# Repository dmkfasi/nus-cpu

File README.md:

# nus-cpu

This is my own yet another attempt to re-create Nintendo 64 motherboard for a portable, tablet or bartop mod.

I am going after for as much as possible: modular design, reuse of original components, cheapest production costs and the best visual display picture.

There are many bright minds out there whose ideas I try to adopt and develop further. But since I lack of expertise on several electronics topics, this whole thing definately will need some tune up.

Feel free to use, share and modify!

# Work in progress
Schematics is not verified so far, but it looks complete and legit and came from a more or less reliable source off a retrogaming community board. Everything has been broken down into following components:
* CPU-RCP defines core:
    * CPU to RCP connections;
    * RCP to PIF (Nintendo peripherials controller);
    * PIF to Controller Pak;
    * Power rails, ENABLE delay and /COLDRESET circuit, decoupling capacitors;
    * and breakout connections to external peripherial devices:
        * Gamepak port, 50pin;
        * RDRAM interface, 30pin;
        * Audio DAC, 4pin;
        * Video DAC, 10pin;
        * and Controller pak (two players), 4pin.
* RCP-RDRAM defines RAM interface:
    * Uses of two or four chips:
        * 2 of RDRAM18;
        * 4 of RDRAM18;
        * 2 of RDRAM36.
    * and onboard MX8330 clock generator;
* RCP-CART defines Gamepak interface, simple board with flat cable connector;
* RCP-SND defines audio output interface, either usage of B9480F or any other DAC and amplifier;
* RCP-VDC will define video interface.

# PCB design and production files
* CPU-RCP is 4 layer board, finished, Gerber files are included;

* RCP-RDRAM is 4 layer board, finished, Gerber files are included;

* RCP-CART is 2 layer board, finished, Gerber files are included;

* RCP-SND is not started yet;
* RCP-VDC is not started yet;

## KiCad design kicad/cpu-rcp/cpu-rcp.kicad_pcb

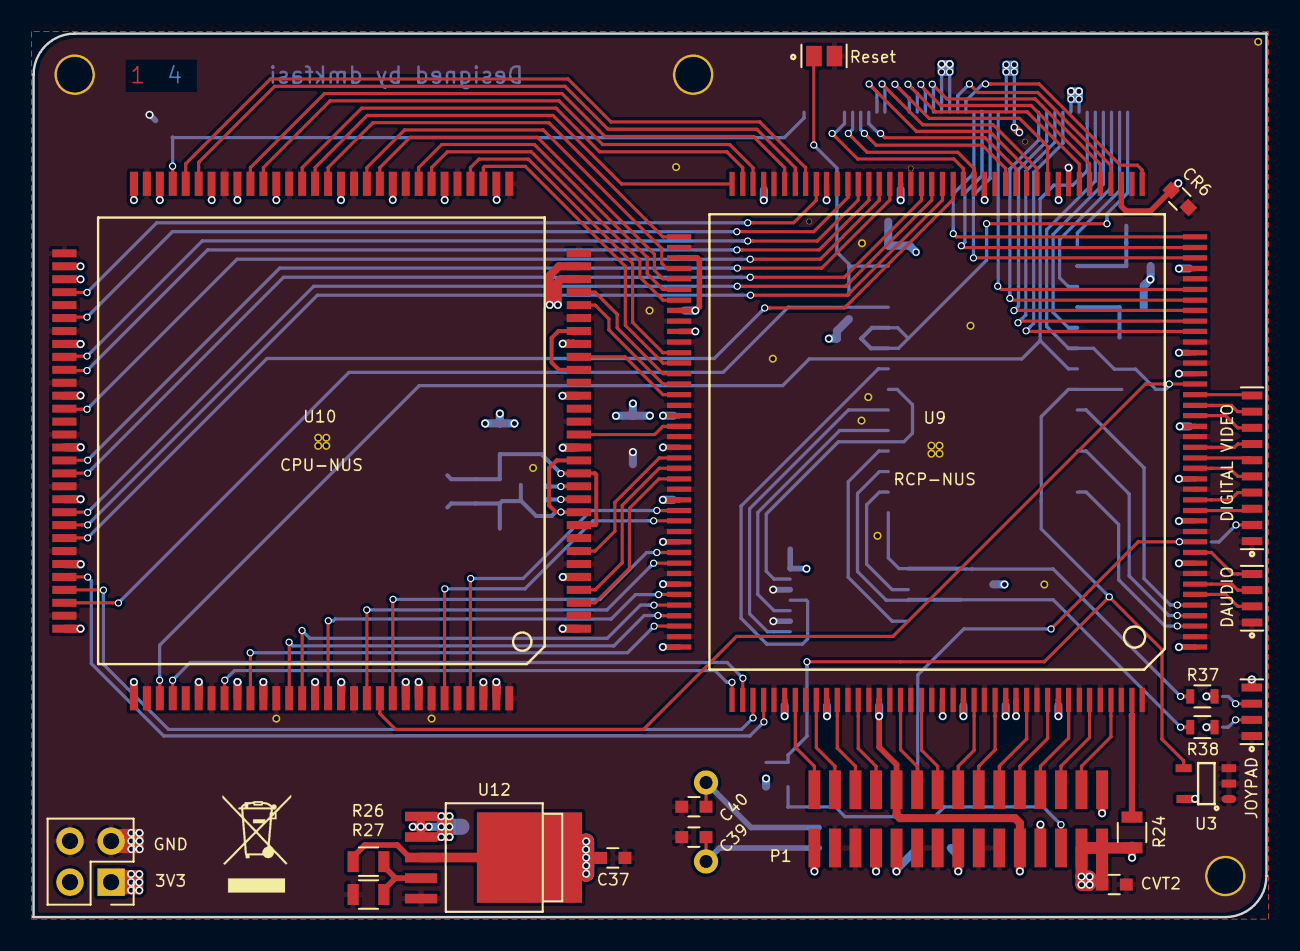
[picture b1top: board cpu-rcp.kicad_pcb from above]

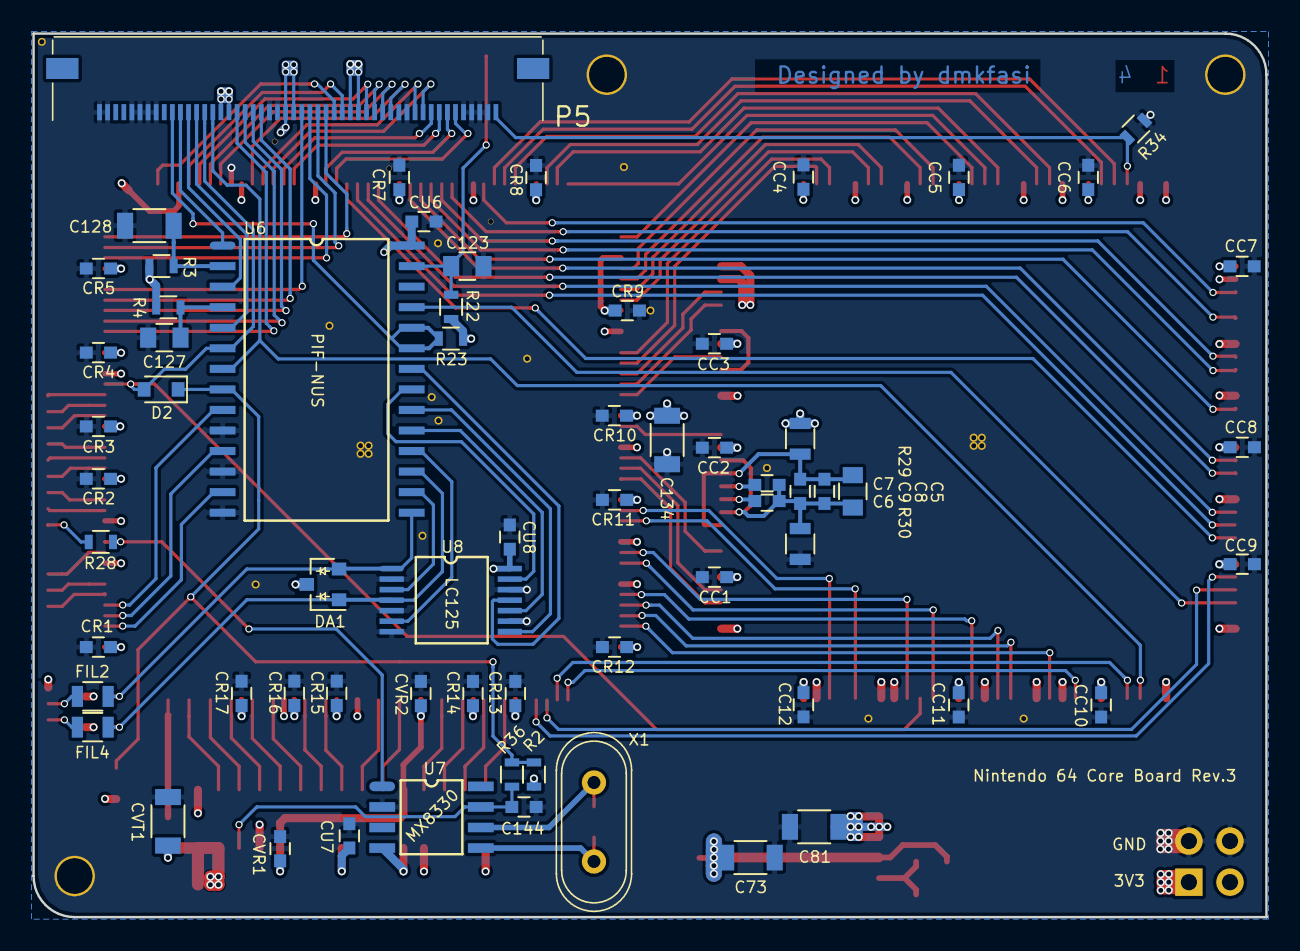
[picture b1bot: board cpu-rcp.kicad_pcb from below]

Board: 4 copper layers, 76.2 x 54.6 mm, 85 parts (65 on the bottom side), 127 nets.

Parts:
C5: C_0805
C6, C7: 220pF; C_0603
C8, C9, C144: C_0603
C37: .1uF; C_0603
C39, C40: 40pF; C_0603
C73, C81, C134: 68uF; C_1206
C123, C127: ±; C_0805
C128: 10uF; C_1206
CC1, CC2, CC3, CC4, CC5, CC6, CC7, CC8, CC9, CC10, CC11, CC12: .1uF; C_0603
CR1, CR2, CR3, CR4, CR5, CR6, CR7, CR8, CR9, CR10, CR11, CR12, CR13, CR14, CR15, CR16, CR17: .1uF; C_0603
CU6, CU7, CU8: .1uF; C_0603
CVR1, CVR2: .1uF; C_0603
CVT1: 10uF; C_1206
CVT2: .1uF; C_0603
D2: ±; D_0805
DA1: BAC54; D_SOT-23_AAK
DAUD1: DAUDIO; Connectors_GS4
DCIN1: Power Input; Pin_Header_Straight_2x02_Pitch2.54mm
DVO1: DIGITAL VIDEO; Connectors_GS10
FIL2, FIL4: 3.3uH; L_0805
JOY1: JOYPAD; Connectors_GS4
P1: RDRAM-EDGE; rdram-edge-smt
P5: 502790-5091; connector-molex-502790-5091
R2: 2K; R_0603
R3: 30K; R_0603
R4: 68K; R_0603
R22, R34: 47K; R_0603
R23: 1K; R_0603
R24: 24R; R_0805
R26: 316; R_0805
R27: 301; R_0805
R28: 0R; R_0603
R29, R30: 4R7; R_0805
R36: 51K; R_0603
R37, R38: 750R; R_0603
SW1: Reset; Connectors_GS2
U3: U3; u3-sot-23-5
U6: PIF-NUS; pif-nus-so-28w
U7: MX8330; mx8330-sop-8
U8: LC125; u8-ssop-14
U9: RCP-NUS; rcp-nus-qfp-160
U10: CPU-NUS; cpu-nus-qfp-120
U12: PQ7VZ5; d-pak-5
X1: 14.318MHz; Crystal_HC-49V

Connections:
+3V3: C81.1, C134.1, CC1.1, CC2.1, CC3.1, CC4.1, CC5.1, CC6.1, CC7.1, CC8.1, CC9.1, CC10.1, CC11.1, CC12.1, CR1.1, CR2.1, CR3.1, CR4.1, CR5.1, CR6.1, CR7.1, CR8.1, CR9.1, CR10.1, CR11.1, CR12.1, CR13.1, CR14.1, CR15.1, CR16.1, CR17.1, CU6.1, CU7.1, CU8.1, DA1.3, DCIN1.1, DCIN1.2, JOY1.4, P1.15, P1.19, P1.23, P1.26, P1.27, P1.30, P5.18, P5.19, P5.26, P5.27, P5.34, P5.35, R2.1, R3.2, R4.2, R22.1, R23.1, R29.2, R37.1, R38.1, U3.5, U6.28, U7.4, U8.14, U9.1, U9.9, U9.13, U9.17, U9.22, U9.27, U9.29, U9.37, U9.43, U9.49, U9.56, U9.64, U9.71, U9.77, U9.83, U9.88, U9.90, U9.98, U9.101, U9.106, U9.110, U9.114, U9.120, U9.126, U9.130, U9.141, U9.143, U9.147, U9.148, U9.152, U10.1, U10.5, U10.15, U10.19, U10.23, U10.28, U10.29, U10.32, U10.36, U10.40, U10.44, U10.49, U10.52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
//EOK: U9.60, U10.82
//PVALID: U9.62, U10.78
/CART_READ: P5.20, U9.44
/CART_WRITE: P5.16, U9.46
/COLDRESET: D2.2, P5.37, U6.6, U9.26, U10.110
/DSYNC: DVO1.3, U9.14
/INT0: U9.80, U10.46
/INT2: U6.25, U10.88
/MasterClock: U9.99, U10.16
/NMI: P5.36, U6.7, U10.93
/SYSAD0: U9.66, U10.73
/SYSAD1: U9.67, U10.70
/SYSAD2: U9.68, U10.69
/SYSAD3: U9.69, U10.66
/SYSAD4: U9.72, U10.64
/SYSAD5: U9.73, U10.56
/SYSAD6: U9.74, U10.55
/SYSAD7: U9.75, U10.51
/SYSAD8: U9.78, U10.50
/SYSAD9: U9.79, U10.47
/SYSAD10: U9.81, U10.45
/SYSAD11: U9.84, U10.42
/SYSAD12: U9.85, U10.41
/SYSAD13: U9.86, U10.38
/SYSAD14: U9.87, U10.37
/SYSAD15: U9.92, U10.34
/SYSAD16: U9.93, U10.33
/SYSAD17: U9.94, U10.27
/SYSAD18: U9.95, U10.26
/SYSAD19: U9.96, U10.22
/SYSAD20: U9.102, U10.7
/SYSAD21: U9.103, U10.4
/SYSAD22: U9.104, U10.3
/SYSAD23: U9.107, U10.117
/SYSAD24: U9.108, U10.115
/SYSAD25: U9.121, U10.98
/SYSAD26: U9.122, U10.94
/SYSAD27: U9.123, U10.87
/SYSAD28: U9.124, U10.86
/SYSAD29: U9.59, U10.83
/SYSAD30: U9.61, U10.81
/SYSAD31: U9.65, U10.77
/SYSCMD0: U9.118, U10.100
/SYSCMD1: U9.117, U10.103
/SYSCMD2: U9.115, U10.106
/SYSCMD3: U9.112, U10.109
/SYSCMD4: U9.111, U10.111
ADDR: P1.12, U9.153
BCLK: DAUD1.2, U9.6
CART_ADDR00: P5.7, U9.57
CART_ADDR01: P5.9, U9.53
CART_ADDR02: P5.11, U9.51
CART_ADDR03: P5.15, U9.47
CART_ADDR04: P5.23, U9.39
CART_ADDR05: P5.25, U9.35
CART_ADDR06: P5.31, U9.33
CART_ADDR07: P5.33, U9.31
CART_ADDR08: P5.32, U9.32
CART_ADDR09: P5.30, U9.34
CART_ADDR10: P5.24, U9.38
CART_ADDR11: P5.22, U9.40
CART_ADDR12: P5.14, U9.50
CART_ADDR13: P5.10, U9.52
CART_ADDR14: P5.8, U9.54
CART_ADDR15: P5.6, U9.58
CART_ALE_H: P5.21, U9.41
CART_ALE_L: P5.17, U9.45
CIC_CLK: P5.40, U6.1
CIC_IN: P5.38, U6.5
CIC_OUT: P5.39, U6.3
CMD: P1.6, U9.137
DQ0: P1.1, U9.127
DQ1: P1.2, U9.129
DQ2: P1.3, U9.131
DQ3: P1.4, U9.133
DQ4: P1.7, U9.139
DQ5: P1.10, U9.149
DQ6: P1.11, U9.151
DQ7: P1.13, U9.155
DQ8: P1.14, U9.157
EEPROM_DAT: P5.41, R23.2, U6.23, U6.24
ENABLE: D2.1, R2.2, R36.2, U3.4, U6.8
ENABLE_CLK: C144.1, P1.18, R36.1, U7.7
GND: C37.2, C39.2, C40.2, C73.2, C81.2, C123.2, C127.2, C128.2, C134.2, C144.2, CC1.2, CC2.2, CC3.2, CC4.2, CC5.2, CC6.2, CC7.2, CC8.2, CC9.2, CC10.2, CC11.2, CC12.2, CR1.2, CR2.2, CR3.2, CR4.2, CR5.2, CR6.2, CR7.2, CR8.2, CR9.2, CR10.2, CR11.2, CR12.2, CR13.2, CR14.2, CR15.2, CR16.2, CR17.2, CU6.2, CU7.2, CU8.2, CVR1.2, CVR2.2, CVT1.2, CVT2.2, DAUD1.1, DCIN1.3, DCIN1.4, DVO1.1, JOY1.1, P1.21, P1.22, P1.24, P1.25, P1.28, P1.29, P5.2, P5.3, P5.4, P5.5, P5.12, P5.13, P5.28, P5.29, P5.43, P5.44, P5.45, P5.46, P5.49, P5.50, R27.2, R30.2, R34.1, SW1.2, U3.1, U3.2, U3.3, U6.10, U6.12, U6.14, U7.2, U8.2, U8.5, U8.7, U8.9, U8.12, U9.2, U9.8, U9.12, U9.16, U9.21, U9.28, U9.30, U9.36, U9.42, U9.48, U9.55, U9.63, U9.70, U9.76, U9.82, U9.89, U9.91, U9.97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
JOY1_DATA: DA1.1, FIL2.1, R37.2, U6.15, U8.1
JOY2_DATA: DA1.2, FIL4.1, R38.2, U6.17, U8.4
JTCK: P5.1, R34.2, U10.57
LRCLK: DAUD1.4, U9.10
unnamed: C5.1, C8.1, C9.1, R29.1, U10.9, U10.13
unnamed: C5.2, C6.2, C7.1, C8.2, C9.2, R30.1, U10.10, U10.14
unnamed: C6.1, U10.11
unnamed: C7.2, U10.12
unnamed: C39.1, U7.5, X1.1
unnamed: C40.1, U7.6, X1.2
unnamed: C123.1, R22.2, SW1.1, U6.27
unnamed: C127.1, R4.1, U6.4
unnamed: C128.1, R3.1, U6.2
unnamed: DVO1.2, R28.2
unnamed: FIL2.2, JOY1.3
unnamed: FIL4.2, JOY1.2
unnamed: R24.2, U9.159
unnamed: R26.2, R27.1, U12.4
unnamed: U6.16, U8.3
unnamed: U6.18, U8.6
unnamed: U6.19, U8.10
unnamed: U6.20, U8.8
unnamed: U6.21, U8.13
unnamed: U6.22, U8.11
unnamed: U10.21, U10.24
unnamed: U9.116, U10.104
PIF_ADR: U6.11, U9.4
PIF_CLK: U6.9, U9.5
PIF_DAT: U6.13, U9.3
RXCLK: P1.9, U9.146
SDAT: DAUD1.3, U9.7
SRGB0: DVO1.10, U9.25
SRGB1: DVO1.9, U9.24
SRGB2: DVO1.8, U9.23
SRGB3: DVO1.7, U9.20
SRGB4: DVO1.6, U9.19
SRGB5: DVO1.5, U9.18
SRGB6: DVO1.4, U9.15
TXCLK: P1.8, U9.144
VCLK: R28.1, U7.1, U9.11
VREF: CVR1.1, CVR2.1, P1.5, P1.20, U9.135
VTERM: C37.1, C73.1, CVT1.1, CVT2.1, P1.16, P1.17, R24.1, R26.1, U12.3

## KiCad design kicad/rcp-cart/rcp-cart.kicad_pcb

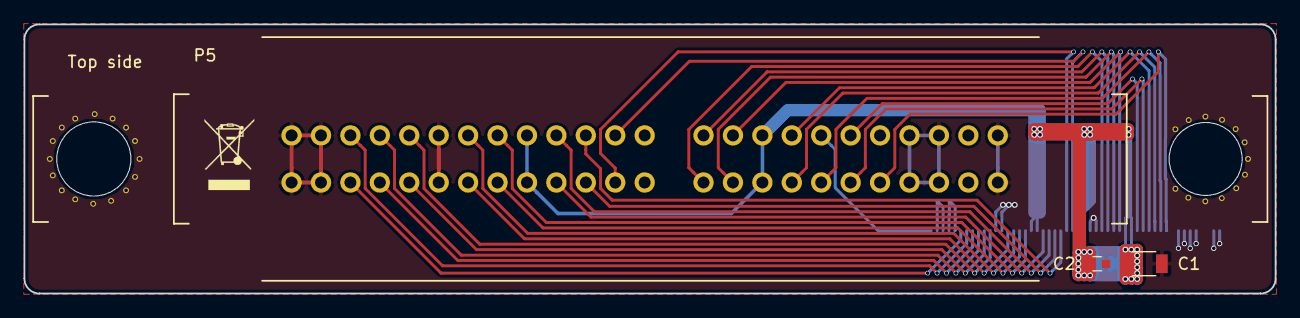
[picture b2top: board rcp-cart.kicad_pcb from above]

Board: 2 copper layers, 106.3 x 22.9 mm, 4 parts (1 on the bottom side), 29 nets.

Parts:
C1: 4.7uF; C_1206
C2: .1uF; C_0603
P5: CART-EDGE; cart-edge-2x25-2.54mm
TO MAIN BOARD: 502790-5091; connector-molex-502790-5091

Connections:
+3V3: C1.1, C2.1, P5.9, P5.17, P5.34, P5.42, TO MAIN BOARD.16, TO MAIN BOARD.17, TO MAIN BOARD.24, TO MAIN BOARD.25, TO MAIN BOARD.32, TO MAIN BOARD.33
//CART_READ: P5.10, TO MAIN BOARD.31
//CART_WRITE: P5.8, TO MAIN BOARD.35
//COLDRESET: P5.20, TO MAIN BOARD.14
//NMI: P5.45, TO MAIN BOARD.15
/CART_ADDR00: P5.28, TO MAIN BOARD.44
/CART_ADDR01: P5.29, TO MAIN BOARD.42
/CART_ADDR02: P5.30, TO MAIN BOARD.40
/CART_ADDR03: P5.32, TO MAIN BOARD.36
/CART_ADDR04: P5.36, TO MAIN BOARD.28
/CART_ADDR05: P5.37, TO MAIN BOARD.26
/CART_ADDR06: P5.40, TO MAIN BOARD.20
/CART_ADDR07: P5.41, TO MAIN BOARD.18
/CART_ADDR08: P5.16, TO MAIN BOARD.19
/CART_ADDR09: P5.15, TO MAIN BOARD.21
/CART_ADDR10: P5.12, TO MAIN BOARD.27
/CART_ADDR11: P5.11, TO MAIN BOARD.29
/CART_ADDR12: P5.7, TO MAIN BOARD.37
/CART_ADDR13: P5.5, TO MAIN BOARD.41
/CART_ADDR14: P5.4, TO MAIN BOARD.43
/CART_ADDR15: P5.3, TO MAIN BOARD.45
/CART_ALE_H: P5.35, TO MAIN BOARD.30
/CART_ALE_L: P5.33, TO MAIN BOARD.34
/CIC_CLK: P5.19, TO MAIN BOARD.11
/EEPROM_DAT: P5.21, TO MAIN BOARD.10
/JTCK: P5.44, TO MAIN BOARD.50
/PIF_CIC_DAT_IN: P5.43, TO MAIN BOARD.13
/PIF_CIC_DAT_OUT: P5.18, TO MAIN BOARD.12
GND: C1.2, C2.2, P5.1, P5.2, P5.6, P5.22, P5.23, P5.25, P5.26, P5.27, P5.31, P5.47, P5.48, P5.50, TO MAIN BOARD.1, TO MAIN BOARD.2, TO MAIN BOARD.5, TO MAIN BOARD.6, TO MAIN BOARD.7, TO MAIN BOARD.8, TO MAIN BOARD.22, TO MAIN BOARD.23, TO MAIN BOARD.38, TO MAIN BOARD.39, TO MAIN BOARD.46, TO MAIN BOARD.47, TO MAIN BOARD.48, TO MAIN BOARD.49

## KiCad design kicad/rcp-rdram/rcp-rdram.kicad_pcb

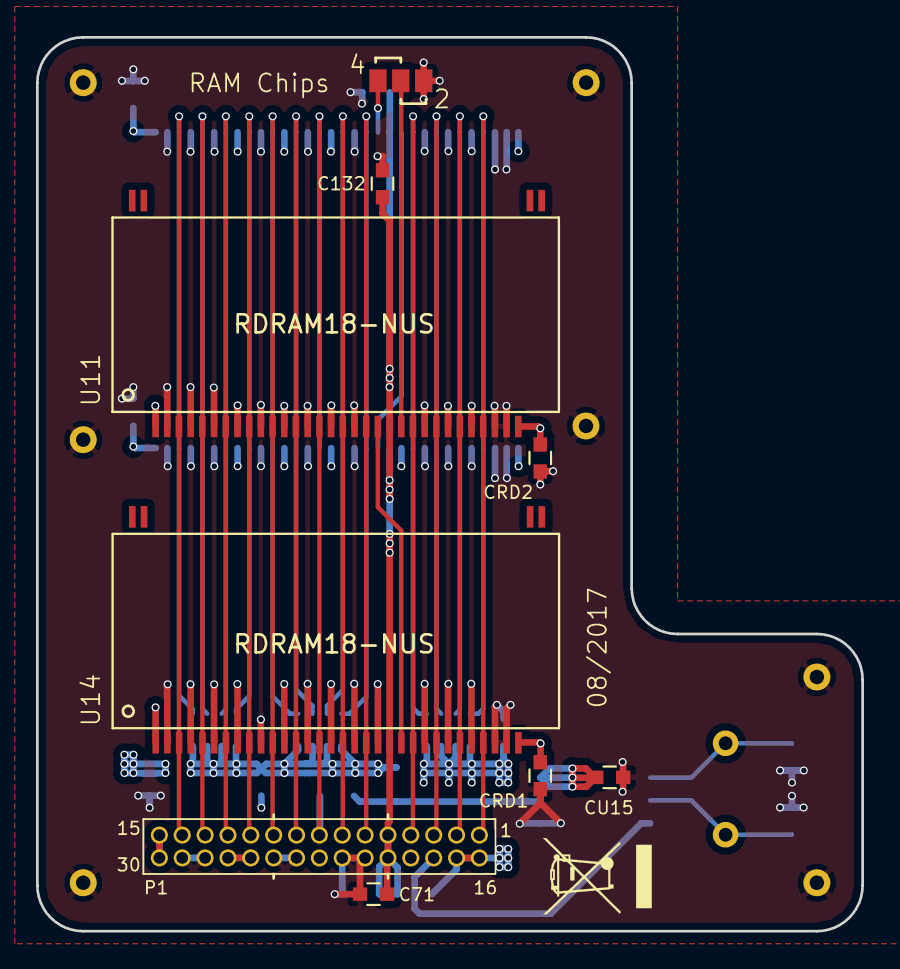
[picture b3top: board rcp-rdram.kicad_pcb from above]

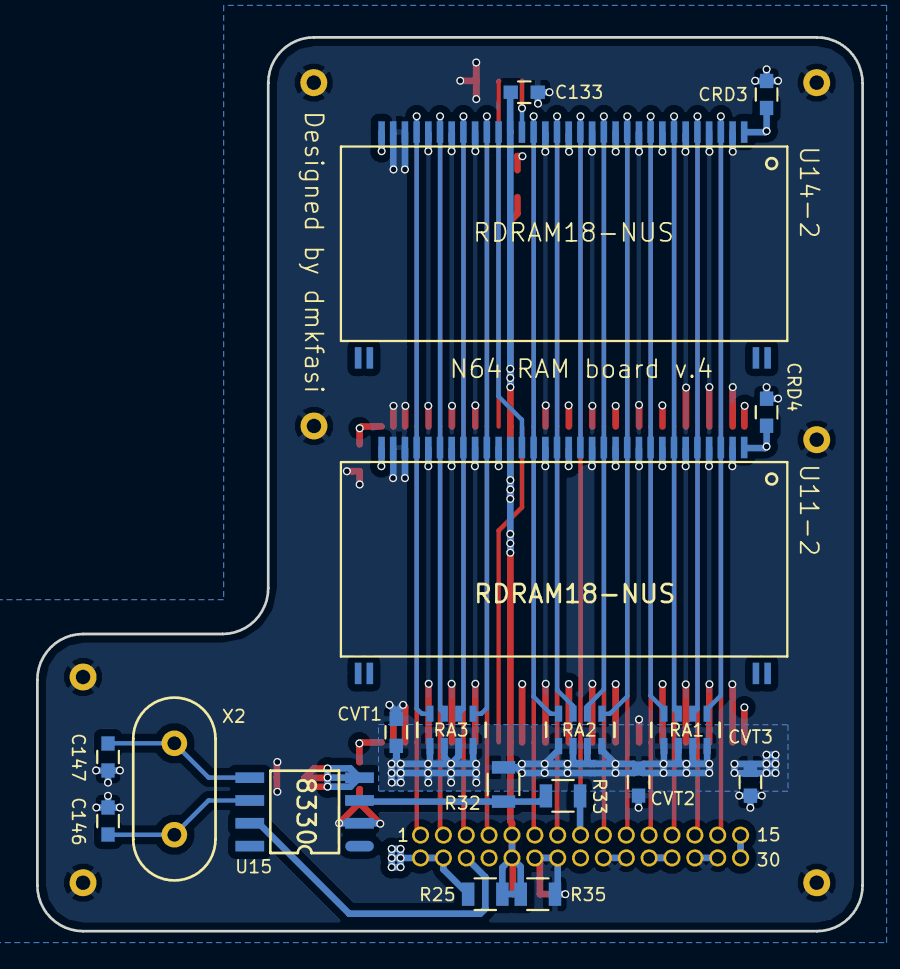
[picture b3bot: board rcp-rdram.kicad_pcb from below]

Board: 4 copper layers, 45.8 x 49.7 mm, 28 parts (19 on the bottom side), 25 nets.

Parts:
C71, C132, C133: C; C_0603
C146, C147: 40pF; C_0603
CRD1, CRD2, CRD3, CRD4: .1uF; C_0603
CU15: .1uF; C_0603
CVT1, CVT2, CVT3: .1uF; C_0603
JP1: 2/4MB RAM; SolderPoint_3P
P1: RDRAM-EDGE; rdram-edge
R25: 130R; R_0805
R32: 150R; R_0805
R33: 33R; R_0805
R35: 390R; R_0805
RA1, RA2, RA3: 51R; cay16-510-j4
U11, U11-2, U14, U14-2: RDRAM18-NUS; rambus-shp-32
U15: 8330; mx8330-sop-8
X2: 14.705MHz; Crystal_HC-49V

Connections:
+3V3: CRD1.1, CRD2.1, CRD3.1, CRD4.1, CU15.2, P1.15, P1.19, P1.23, P1.26, P1.27, P1.30, U11.1, U11.8, U11.12, U11.16, U11.32, U11-2.1, U11-2.8, U11-2.12, U11-2.16, U11-2.32, U14.1, U14.8, U14.12, U14.16, U14.20, U14.32, U14-2.1, U14-2.8, U14-2.12, U14-2.16, U14-2.32, U15.4
/ADDRESS: P1.12, RA1.3, U11.7, U11-2.7, U14.7, U14-2.7
/COMMAND: P1.6, RA2.4, U11.19, U11-2.19, U14.19, U14-2.19
/DQ0: P1.1, RA3.4, U11.29, U11-2.29, U14.29, U14-2.29
/DQ1: P1.2, RA3.3, U11.27, U11-2.27, U14.27, U14-2.27
/DQ2: P1.3, RA3.2, U11.25, U11-2.25, U14.25, U14-2.25
/DQ3: P1.4, RA3.1, U11.23, U11-2.23, U14.23, U14-2.23
/DQ4: P1.7, RA2.3, U11.17, U11-2.17, U14.17, U14-2.17
/DQ5: P1.10, RA2.1, U11.11, U11-2.11, U14.11, U14-2.11
/DQ6: P1.11, RA1.4, U11.9, U11-2.9, U14.9, U14-2.9
/DQ7: P1.13, RA1.2, U11.5, U11-2.5, U14.5, U14-2.5
/DQ8: P1.14, RA1.1, U11.3, U11-2.3, U14.3, U14-2.3
/ENABLE: P1.18, U15.7
/RXCLK: P1.9, RA2.2, U11.13, U11-2.13, U14.13, U14-2.13
/TXCLK: P1.8, R33.1, U11.15, U11-2.15, U14.15, U14-2.15
/VREF: C71.1, C132.1, C133.1, P1.5, P1.20, R25.2, R35.1, U11.21, U11-2.21, U14.21, U14-2.21
/VTERM: CVT1.2, CVT2.2, CVT3.2, P1.16, P1.17, R25.1, R32.2, RA1.5, RA1.6, RA1.7, RA1.8, RA2.5, RA2.6, RA2.7, RA2.8, RA3.5, RA3.6, RA3.7, RA3.8
GND: C71.2, C132.2, C133.2, C146.2, C147.2, CRD1.2, CRD2.2, CRD3.2, CRD4.2, CU15.1, CVT1.1, CVT2.1, CVT3.1, JP1.3, P1.21, P1.22, P1.24, P1.25, P1.28, P1.29, R35.2, U11.2, U11.4, U11.6, U11.10, U11.14, U11.18, U11.24, U11.26, U11.28, U11.30, U11.31, U11-2.2, U11-2.4, U11-2.6, U11-2.10, U11-2.14, U11-2.18, U11-2.22, U11-2.24, U11-2.26, U11-2.28, U11-2.30, U11-2.31, U14.2, U14.4, U14.6, U14.10, U14.14, U14.18, U14.24, U14.26, U14.28, U14.30, U14.31, U14-2.2, U14-2.4, U14-2.6, U14-2.10, U14-2.14, U14-2.18, U14-2.24, U14-2.26, U14-2.28, U14-2.30, U14-2.31, U15.2
unnamed: C146.1, U15.6, X2.2
unnamed: C147.1, U15.5, X2.1
unnamed: JP1.1, U14-2.20
unnamed: JP1.2, U11.22
unnamed: R32.1, R33.2, U15.3
unnamed: U11-2.20, U14-2.22
unnamed: U11.20, U14.22

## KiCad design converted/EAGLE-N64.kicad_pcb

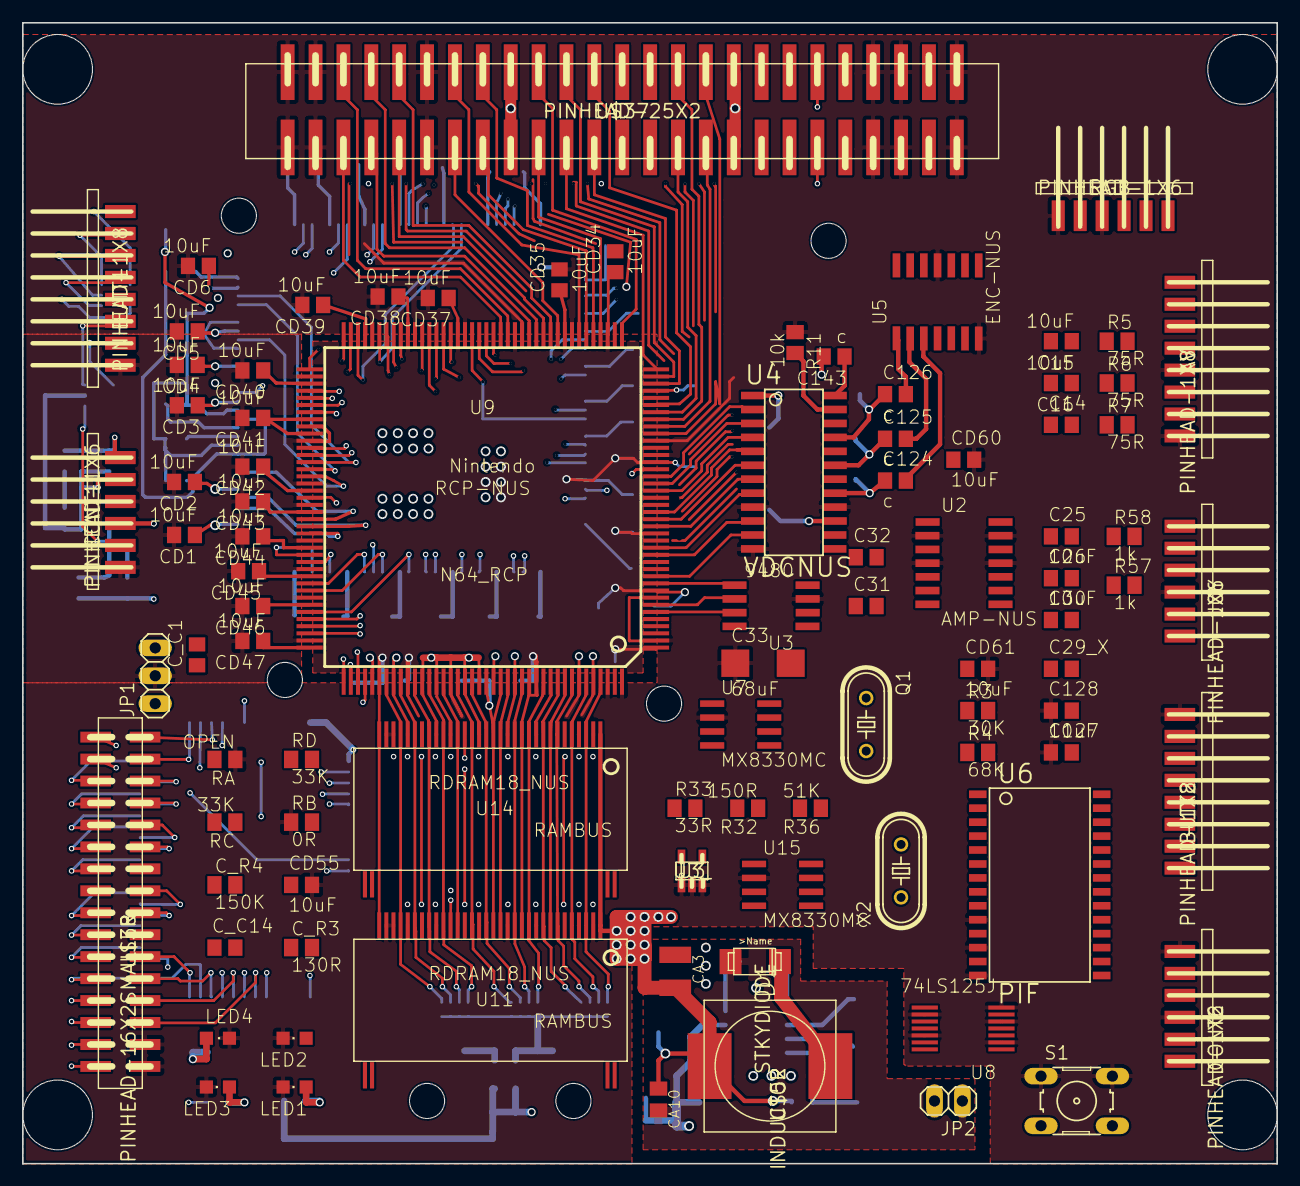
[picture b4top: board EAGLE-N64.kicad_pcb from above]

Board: 4 copper layers, 114.3 x 103.9 mm, 226 parts (0 on the bottom side), 239 nets.

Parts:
3V3: LM22680; PSOP-8
@HOLE0, @HOLE1, @HOLE2, @HOLE3, @HOLE4, @HOLE5, @HOLE6, @HOLE7, @HOLE8, @HOLE9: (no value)
AV: PINHEAD-1X8; 2MMPINHEAD-1X8
BUTT1, BUTT2: PINHEAD-1X8; 2MMPINHEAD-1X8
C5: C0805K
C6, C7, C8, C9, C11, C12, C13, C14, C21, C23, C29_X, C30, C31, C32, C39, C40_, C122, C123, C127, C132, C144, C146, C147, C155, C156, C157, C158: C0805
C15, C16, C24, C25, C26, C28, C34, C128: 10uF; C0805
C33: 68uF; C%2f6032-28R
C124, C125, C126, C143: c; C0805
CA, CA1, CA4: C1206K
CA2, CA5, CA7, CA8, CA10, CA11, CA12: C0805K
CA3: C1210K
CA6, CA9: 470pF; C0805K
CD1, CD2, CD3, CD4, CD5, CD6, CD7, CD8, CD9, CD10, CD11, CD12, CD13, CD14, CD15, CD16, CD17, CD18, CD19, CD20, CD21, CD22, CD23, CD24, CD25, CD26, CD27, CD28, CD29, CD30, CD31, CD32, CD33, CD34, CD35, CD36, CD37, CD38, CD39, CD40, CD41, CD42, CD43, CD44, CD45, CD46, CD47, CD48, CD49, CD50, CD51, CD52, CD54, CD55, CD56, CD57, CD58, CD59, CD60, CD61: 10uF; C0805
CONT1, CONT2: PINHEAD-1X6; 2MMPINHEAD-1X6
C_C1, C_C14: C0805
C_R1: 1M0; M0805
C_R3: 130R; M0805
C_R4: 150K; M0805
C_U1: CNT-NUS; PQFP64
D1, D2: PMLL4150; SOD80C
D1#2: STKYDIODE
JOY: PINHEAD-1X6; 2MMPINHEAD-1X6
JP1: 1X03
JP2: 1X02
LED1, LED2, LED3, LED4: CHIPLED_0805
Q1: HC49%2fS
R2: 2k0; M0805
R3: 30K; M0805
R4: 68K; M0805
R5, R6, R7: 75R; M0805
R8, R9, R10: 110R; M0805
R11, R18, R20, R23: 10k; M0805
R12: 820R; M0805
R13: 4k3; M0805
R17: 1K; M0805
R19: 180k; M0805
R21, R57, R58: 1k; M0805
R22, R34: 47K; M0805
R24: 24R; M0805
R25, R53, R54, R55, R56: 130R; M0805
R29, R30: 4R7; M0805
R32: 150R; M0805
R33: 33R; M0805
R35: 390R; M0805
R36: 51K; M0805
R37, R38, R39, R40: 750R; M0805
RA: OPEN; M0805
RB: 0R; M0805
RC: 33K; M0805
RD: 33K; M0805
RE, RE1, RE2, RE3, RE4: 1K4; M0805
RF: 1K0; M0805
RG: 191k; M0805
RGB: PINHEAD-1X6; 2MMPINHEAD-1X6
RN1, RN2, RN3: RESNET; RESARRAY
S1: B3F-10XX
TVS1, TVS2, TVS3, TVS4, TVS5, TVS6: TVS; SC-74
U2: AMP-NUS; SO14
U3: 9480; SO8
U3_: U3; SOT23-5
U4: VDCNUS; SO24
U5: ENC-NUS; SO14
U6: PIF; SO28W
U7, U15: MX8330MC; SO08
U8: 74LS125J; QSOP14
U9: N64_RCP; PQFP160
U10: R4300_CPU; QFP120
U11, U14: RDRAM18_NUS; SHP32
U12, U13: MIC5219; SOT23-5
U$37: PINHEAD-25X2
U$38: PINHEAD-16X2SMALLER; 2MMPINHEAD-16X2
U$52: INDUCTOR
X2: HC49%2fS

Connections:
3V3: C143.2, C155.2, C156.2, C157.2, C158.2, CA3.2, CA4.2, CA10.1, CD1.1, CD2.1, CD3.1, CD4.1, CD5.1, CD6.1, CD7.1, CD8.1, CD9.1, CD10.1, CD11.1, CD12.1, CD13.1, CD14.1, CD15.1, CD16.1, CD17.1, CD18.1, CD19.1, CD20.1, CD21.1, CD22.1, CD23.1, CD24.1, CD25.1, CD26.1, CD27.1, CD28.1, CD29.1, CD30.1, CD31.1, CD32.1, CD33.1, CD34.1, CD35.1, CD36.1, CD37.1, CD38.1, CD39.1, CD40.1, CD41.1, CD42.1, CD43.1, CD44.1, CD45.1, CD46.1, CD47.1, CD48.1, CD49.1, CD50.1, CD51.1, CD52.1, CD54.1, CD55.1, CD56.1, CD57.1, CD58.1, CONT1.3, CONT1.6, CONT2.3, CONT2.6, C_C14.2, C_R4.1, C_U1.1, C_U1.11, C_U1.33, C_U1.40, C_U1.64, JOY.5, R2.2, R3.2, R4.2, R22.2, R23.1, R29.2, R34.2, R37.1, R38.1, R39.1, R40.1, RC.2, RD.2, RE.1, RE3.2, U3.8, U3_.5, U4.1, U4.15, U6.28, U7.4, U8.14, U9.1, U9.9, U9.13, U9.17, U9.22, U9.27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
+5V: AV.1, CA5.2, CD59.1, CD60.1, RE2.2, RGB.5, U5.4, U5.9, U5.14, U13.5
+12V: 3V3.7, CA1.2, CA2.2, CA7.2, CA11.1, CD61.1, JP2.2, RE1.2, U2.8, U12.1, U12.3, U13.1, U13.3, U$37.25, U$37.26
/COLDRESET: D2.A, U6.6, U9.26, U10.110, U$37.39
/INT2: U6.25, U10.88
ADJ: 3V3.4, RE.2, RF.1
C16X: C16.1, R6.2
C_C11: C_C1.1, C_R1.2, JP1.1
DQ0: RN1.1, U9.127, U11.29, U14.29
DQ1: RN1.2, U9.129, U11.27, U14.27
DQ2: RN1.3, U9.131, U11.25, U14.25
DQ3: RN1.4, U9.133, U11.23, U14.23
DQ4: RN2.2, U9.139, U11.17, U14.17
DQ5: RN2.4, U9.149, U11.11, U14.11
DQ6: RN3.1, U9.151, U11.9, U14.9
DQ7: RN3.3, U9.155, U11.5, U14.5
DQ8: RN3.4, U9.157, U11.3, U14.3
FROM_U15: D1.C, D2.C, R2.1, R19.1, R36.2, U3_.4, U6.8
FSEL: C144.2, R36.1, U7.7, U15.7
FSO1: R32.1, R33.2, U15.3
GND: 3V3.6, 3V3.9, AV.5, AV.8, BUTT1.1, BUTT2.1, C11.2, C12.2, C13.2, C23.2, C24.1, C28.1, C33.-, C34.1, C39.2, C40_.2, C122.2, C123.2, C127.1, C128.1, C132.2, C144.1, C146.2, C147.2, CA1.1, CA2.1, CA3.1, CA4.1, CA5.1, CA6.1, CA7.1, CA8.1, CA9.1, CA10.2, CA11.2, CA12.1, CD1.2, CD2.2, CD3.2, CD4.2, CD5.2, CD6.2, CD7.2, CD8.2, CD9.2, CD10.2, CD11.2, CD12.2, CD13.2, CD14.2, CD15.2, CD16.2, CD17.2, CD18.2, CD19.2, CD20.2, CD21.2, CD22.2, CD23.2, CD24.2, CD25.2, CD26.2, CD27.2, CD28.2, CD29.2, CD30.2, CD31.2, CD32.2, CD33.2, CD34.2, CD35.2, CD36.2, CD37.2, CD38.2, CD39.2, CD40.2, CD41.2, CD42.2, CD43.2, CD44.2, CD45.2, CD46.2, CD47.2, CD48.2, CD49.2, CD50.2, CD51.2, CD52.2, CD54.2, CD55.2, CD56.2, CD57.2, CD58.2, CD59.2, CD60.2, CD61.2, CONT1.1, CONT1.4, CONT2.1, CONT2.4, C_U1.18, C_U1.19, C_U1.32, C_U1.52, C_U1.57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
INT0: U9.80, U10.46
LEFT_AUDIO: C30.1, R21.2, U$37.47
unnamed: C156.1, R54.2
unnamed: C155.1, R53.2
unnamed: U4.11, U7.1, U9.11
unnamed: R24.1, U9.159
unnamed: C147.1, Q1.2, U7.5
unnamed: C146.1, Q1.1, U7.6
unnamed: BUTT1.2, C_U1.20, TVS3.1
unnamed: RGB.2, U4.22
unnamed: RGB.4, U4.20
unnamed: U6.9, U9.5
unnamed: U6.11, U9.4
unnamed: U6.13, U9.3
unnamed: TVS2.1, U6.15, U8.1
unnamed: CONT1.5, C_R3.2, C_R4.2, C_U1.22, C_U1.23, R37.2, R53.1, TVS3.5, U6.16, U8.3
unnamed: BUTT1.3, C_U1.10, TVS3.6
unnamed: LED1.A, RE1.1
unnamed: CONT1.2, R38.2, R54.1, TVS3.4, U6.18, U8.6
unnamed: TVS2.4, U6.19, U8.10
unnamed: CONT2.5, R39.2, R55.1, TVS4.4, U6.20, U8.8
unnamed: TVS2.3, U6.21, U8.13
unnamed: CONT2.2, R40.2, R56.1, TVS4.5, U6.22, U8.11
unnamed: U4.2, U9.25
unnamed: U9.116, U10.104
unnamed: TVS2.6, U6.17, U8.4
unnamed: U9.62, U10.78
unnamed: U9.60, U10.82
unnamed: C123.1, R22.1, S1.3, S1.4, U6.27
unnamed: U4.3, U9.24
unnamed: RB.2, RC.1, U10.116
unnamed: U9.39, U$37.22
unnamed: RA.2, RD.1, U10.112
unnamed: U9.58, U$37.5
unnamed: U9.57, U$37.6
unnamed: U9.54, U$37.7
unnamed: U9.53, U$37.8
unnamed: U9.52, U$37.9
unnamed: U9.51, U$37.10
unnamed: U9.99, U10.16
unnamed: U9.50, U$37.13
unnamed: U9.47, U$37.14
unnamed: U9.46, U$37.15
unnamed: U9.45, U$37.16
unnamed: U9.44, U$37.19
unnamed: U9.41, U$37.20
unnamed: U9.38, U$37.23
unnamed: U9.35, U$37.24
unnamed: U9.34, U$37.29
unnamed: U9.33, U$37.30
unnamed: U9.32, U$37.31
unnamed: U9.31, U$37.32
unnamed: C157.1, R55.2
unnamed: U6.5, U$37.35
unnamed: U6.3, U$37.36
unnamed: U6.1, U$37.37
unnamed: R23.2, U6.23, U6.24, U$37.41
unnamed: C5.1, C8.1, C9.1, R29.1, U10.9, U10.13
unnamed: C5.2, C6.1, C7.1, C8.2, C9.2, R30.2, U10.10, U10.14
unnamed: C6.2, U10.11
unnamed: C7.2, U10.12
unnamed: U10.21, U10.24
unnamed: U3.5, U9.10
unnamed: U3.6, U9.7
unnamed: U3.7, U9.6
unnamed: C33.+, U3.2
unnamed: C127.2, R4.1, U6.4
unnamed: C128.2, R3.1, U6.2
unnamed: U4.4, U9.23
unnamed: U4.5, U9.20
unnamed: U4.6, U9.19
unnamed: U4.7, U9.18
unnamed: U4.8, U9.15
unnamed: U4.10, U9.14
unnamed: R11.2, U4.23
unnamed: C126.1, R10.2, U4.21
unnamed: R34.1, U10.57, U$37.38
unnamed: C32.1, R20.2, U3.4
unnamed: C31.1, R18.2, U3.1
unnamed: C143.1, U4.24
unnamed: C125.1, R9.2, U4.19
unnamed: C124.1, R8.2, U4.17
unnamed: C158.1, R56.2
unnamed: C32.2, C34.2, U2.5
unnamed: C31.2, U2.10
unnamed: C24.2, U2.7
unnamed: C28.2, U2.9
unnamed: C29_X.2, U2.12
unnamed: C30.2, U2.3
unnamed: D1.A, R19.2, U2.6
unnamed: C25.1, R58.2
unnamed: C14.1, U5.10
unnamed: C26.2, U2.14
unnamed: AV.7, C122.1, R57.1, TVS1.3
unnamed: C26.1, R57.2
unnamed: C_U1.56, U$38.1
unnamed: CA6.2, U13.4
unnamed: C_U1.55, U$38.2
unnamed: U4.13, U5.6
unnamed: U4.14, U5.5, U$37.42
unnamed: C124.2, U5.3
unnamed: C125.2, U5.2
unnamed: C126.2, U5.1
unnamed: C15.1, R5.2
unnamed: C15.2, U5.13
unnamed: C16.2, U5.12
unnamed: AV.4, C11.1, R7.1, TVS1.5
unnamed: AV.3, C12.1, R6.1
unnamed: C14.2, R7.2
unnamed: C21.1, U5.8
unnamed: R13.2, U7.8
unnamed: C21.2, R12.2, R13.1
unnamed: AV.2, C13.1, R5.1, TVS1.1, TVS1.6
unnamed: RGB.6, U4.18
unnamed: C_U1.8, JOY.1
unnamed: C_U1.54, U$38.3
unnamed: C_U1.53, U$38.4
unnamed: C_U1.9, JOY.2
unnamed: C_U1.51, U$38.5
unnamed: C_U1.49, U$38.6
unnamed: C_U1.48, U$38.7
unnamed: C_U1.47, U$38.8
unnamed: U9.40, U$37.21
unnamed: C_U1.46, U$38.9
unnamed: C_U1.45, U$38.11
unnamed: C_U1.44, U$38.10
unnamed: C_U1.43, U$38.12
unnamed: C_U1.42, U$38.13
unnamed: C_U1.41, U$38.14
unnamed: BUTT2.2, C_U1.21, TVS6.1
unnamed: C_U1.38, U$38.16
unnamed: C_U1.37, U$38.18
unnamed: C_U1.39, U$38.17
unnamed: C_U1.36, U$38.19
unnamed: C_U1.35, U$38.20
unnamed: C_U1.34, U$38.21
unnamed: C_U1.31, U$38.22
unnamed: C_U1.30, U$38.23
unnamed: C_U1.29, U$38.24
unnamed: C_U1.28, U$38.25
unnamed: C_U1.27, U$38.26
unnamed: C_U1.26, U$38.27
unnamed: C_U1.25, U$38.28
unnamed: C_U1.24, U$38.29
unnamed: C_C14.1, C_R3.1
unnamed: 3V3.2, CA12.2
unnamed: BUTT2.3, C_U1.17, TVS6.6
unnamed: BUTT2.4, C_U1.16, TVS6.5
unnamed: BUTT2.5, C_U1.15, TVS6.4
unnamed: BUTT2.6, C_U1.14, TVS6.3
unnamed: BUTT2.7, C_U1.13, TVS4.1
unnamed: BUTT2.8, C_U1.12, TVS4.6
unnamed: C_U1.7, JOY.3
unnamed: C_U1.6, JOY.6
unnamed: BUTT1.4, C_U1.5, TVS5.3
unnamed: BUTT1.5, C_U1.4, TVS5.4
unnamed: BUTT1.6, C_U1.3, TVS5.5
unnamed: BUTT1.7, C_U1.2, TVS5.6
unnamed: BUTT1.8, C_U1.58, TVS5.1
unnamed: C_R1.1, C_U1.61, JP1.3
unnamed: C_C1.2, C_U1.63
unnamed: CA9.2, U12.4
unnamed: 3V3.3, RG.1
unnamed: 3V3.1, CA.1
unnamed: LED2.A, RE2.1
unnamed: LED4.A, RE4.1
unnamed: LED3.A, RE3.1
NMI: U6.7, U10.93, U$37.40
OSCIN1: C39.1, U15.6, X2.1
OSCOUT1: C40_.1, U15.5, X2.2
R58: AV.6, C23.1, R58.1, TVS1.4
RAM0: C132.1, R25.1, R35.2, U9.135, U11.21, U14.21
RAM1: RN2.1, U9.137, U11.19, U14.19
RAM2: R33.1, U9.144, U11.15, U14.15
RAM3: RN2.3, U9.146, U11.13, U14.13
RAM4: RN3.2, U9.153, U11.7, U14.7
RIGHT_AUDIO: C29_X.1, R17.2, U$37.48
SW: 3V3.8, CA.2, D1#2.-, U$52.1
SYSAD0: U9.66, U10.73
SYSAD1: U9.67, U10.70
SYSAD2: U9.68, U10.69
SYSAD3: U9.69, U10.66
SYSAD4: U9.72, U10.64
SYSAD5: U9.73, U10.56
SYSAD6: U9.74, U10.55
SYSAD7: U9.75, U10.51
SYSAD8: U9.78, U10.50
SYSAD9: U9.79, U10.47
SYSAD10: U9.81, U10.45
SYSAD11: U9.84, U10.42
SYSAD12: U9.85, U10.41
SYSAD13: U9.86, U10.38
SYSAD14: U9.87, U10.37
SYSAD15: U9.92, U10.34
SYSAD16: U9.93, U10.33
SYSAD17: U9.94, U10.27
SYSAD18: U9.95, U10.26
SYSAD19: U9.96, U10.22
SYSAD20: U9.102, U10.7
SYSAD21: U9.103, U10.4
SYSAD22: U9.104, U10.3
SYSAD23: U9.107, U10.117
SYSAD24: U9.108, U10.115
SYSAD25: U9.121, U10.98
SYSAD26: U9.122, U10.94
SYSAD27: U9.123, U10.87
SYSAD28: U9.124, U10.86
SYSAD29: U9.59, U10.83
SYSAD30: U9.61, U10.81
SYSAD31: U9.65, U10.77
SYSCMD0: U9.118, U10.100
SYSCMD1: U9.117, U10.103
SYSCMD2: U9.115, U10.106
SYSCMD3: U9.112, U10.109
SYSCMD4: U9.111, U10.111
U2: C25.2, U2.1
U3: U11.22, U14.20
VTERM: CA8.2, R24.2, R25.2, R32.2, RE4.2, RN1.5, RN1.6, RN1.7, RN1.8, RN2.5, RN2.6, RN2.7, RN2.8, RN3.5, RN3.6, RN3.7, RN3.8, U12.5

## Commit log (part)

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2017-01-15 Playing around
2017-01-16 Amphenol FCI 62684-50110E9ALF, flat cable connector for CART EDGE, 50pins, 0.5mm pitch
2017-01-18 Design Rules setting changed to fit better board and fab process
2017-01-18 Shortened pin counter
2017-01-18 Fixed RESNET pinout to match current footprint of CAY16-J4
2017-01-18 Redo signal termination (a major fail here), power supply lines, going to rewire for 0.1524mm (8mil) line clearance
2017-01-18 Get rid of outdated files
2017-01-19 Moved for more appropriate naming scheme
2017-01-19 Get back to 0.2mm line space Design Rule
2017-01-19 Board changed to L-shape, moved top side RDRAM chips to trick difficult to connect SOUT pin, rewired VREF resistor devider, other improvements
2017-01-20 This image turned out to be -05-1 revision with MAV-NUS video DAC
2017-01-20 Dimensions added, capacitors moved around, getting ready to shrink the board
2017-01-20 Revision 2, mostly finished, TODO: checks
2017-01-20 Text size reduced
2017-01-20 More stitchings for VREF line, minor text cleanups
2017-01-21 Minor cleanups
2017-01-22 PDF doc reference added
2017-01-22 Redrawn with actual connector size, mounting holes and outlines
2017-01-22 Useless
2017-01-22 More convenient node name for better bash navigation
2017-01-22 OSH Park PCB images designed by Michael Chen
2017-01-22 AMPHENOL flat cable 50 pin 0.5mm pitch for connecting CART EDGE
2017-01-22 Well, it actually revision 08 and not 05
2017-01-22 Cleaning up
2017-01-22 Cleanup
2017-01-22 Changed DC input capacitors to 1206 size
2017-01-22 Footprints updated, using AMP connector for CART EDGE now
2017-01-22 Mixed up fab name
2017-01-22 Footprints updated
2017-01-22 Wizard generated 4 pins 1.0mm pitch FPC for audio
2017-01-22 New name for CART EDGE breakout connector
2017-01-22 Accidently renamed, gotta rid of it
2017-01-22 Dedicated PIF-NUS footprint
2017-01-22 Removed Dwgs.User
2017-01-23 Old stuff
2017-01-24 Corrected Fab name
2017-01-24 Now using Hirose DF13 1.25mm pitch SMT connector for power input
2017-01-24 Still playing around
2017-01-24 Fixed CART EDGE connector foorprint, replaced VIDEO OUT with Hirose DF52, the same type as AUDIO OUT
2017-01-26 Molex 50 pins 0.5mm pitch for CART EDGE connector
2017-01-26 Re-assigned FPC connectors, now using unified Molex 505110 series, see datasheet for details
2017-01-26 Molex FPC 505110 series, 0.5mm pitch
2017-01-26 Files cleanup
2017-01-26 Molex 502790 series 50 pins 0.5mm pitch to hook CART EDGE
2017-01-29 Filename corrected
2017-01-29 Power supply mating 02x03 pins, 2.0mm pitch
2017-01-29 Molex power input jack
2017-01-29 3D shape, exported from official STEP with FreeCAD
2017-01-29 Using new foorprints
2017-01-29 3D shapes for all the Molex connectors used
2017-01-29 3D shapes added and scaled
2017-01-29 Now using Molex 3D shapes
2017-01-31 Current netlist has been read
2017-01-31 PIF added
2017-01-31 External connections sheet added
2017-01-31 Current settings
2017-01-31 PIF-NUS redrawn for better pinout, changes to CARTEDGE for PIF connections, PushButton for RESET added
2017-01-31 CARTEDGE PIF-CIC connection changes, PIF connector removed
2017-01-31 #COLDRESET D2 diode down to ENABLE signal added
2017-02-05 Modified RDRAM EDGE for better VREF, VTERM and 3V3 pinout
2017-02-05 Now using modified RDRAM EDGE pinout
2017-02-05 Better fit of VREF Resistor divider using new RDRAM EDGE pinout, some other small improvements related to the power rails
2017-02-05 Now using new RDRAM EDGE. RDRAM EDGE moved to external connections sheet
2017-02-05 Slightly adjusted with new RDRAM EDGE footprints
2017-02-05 Better footprint layout for M50-3001545
2017-02-16 Prelimary 3D shape for RDRAM chip SHP-32 package, FreeCAD source file
2017-02-16 Preliminary 3D shape for RDRAM chip SHP-32 package, FreeCAD source file
2017-02-17 RDRAM 3D shape added on adjusted scale
2017-02-18 Adjusted scale to correct value of 0.3937
2017-02-18 RDRAM 3D shape
2017-02-19 Slightly modified pads clearance, according to actual measurements
2017-02-19 All the pads were shortened according to datasheet specs, to save PCB space as well
2017-02-19 Updated look with RDRAM chip rendered
2017-02-19 Board mechanical layout
2017-02-19 Color coated
2017-02-19 FreeCAD file out of STP, painted
2017-02-19 Moved to appropriate directory
2017-02-19 RDRAM EDGE 3D shape
2017-02-19 Colors coated
2017-02-19 Updated look
2017-02-19 Updated with RDRAM EDGE 3D shape
2017-02-19 Converted from STP
2017-02-19 Mating SMT connector for Main PCB RDRAM EDGE
2017-02-19 Correct naming scheme
2017-02-19 Mating profiles reference
2017-02-19 Fully rendered, finally. TODO coat with proper colors
2017-02-19 Fixed disappearing after export to VRML
2017-02-21 Colorized
2017-02-21 Better colorization
2017-02-21 3D shape position adjusted
2017-02-21 Moving around
2017-02-21 Rebuild to utilize new 3D shapes
2017-02-21 Future reference for RCP-NUS QFP-160 package 3D shape recreation
2017-02-21 Pin designators added on the back silkscreen
2017-02-21 Adjusted 3D shape angle and offset
2017-02-21 Changed footprint for RDRAM EDGE to m50-3601542
2017-02-22 Mechanical design reference for QFP-160 3D shape
2017-02-22 Got rid in flavor of PDFs under datasheet folder
2017-02-22 Harwin M50-3601542 footprint for RDRAM EDGE at CPU-RCP board side
2017-02-22 RDRAM EDGE SMT for CPU-RCP board side
2017-02-23 Pin size and body offset adjusted
2017-02-23 RCP-NUS 3D shape
2017-02-24 Completed 3D shape for RCP-NUS
2017-02-24 Complete FreeCAD model for RCP-NUS QFP-160
2017-02-24 Accumulated all 3D shapes for local storage
2017-02-24 Replaced duplicate footprint
2017-02-24 QFP-64 14x20mm footprint reference for CNT-NUS
2017-02-25 Rephrased a little
2017-03-02 Laying around, WIP
2017-03-02 Changed decoupler capacitors footprints to 0603 size
2017-08-17 N64 portable PCB designs by Marshall
2017-08-17 Moved to apropriate place
2017-08-17 Reduced number of decoupling capacitors for both CPU and RCP
2017-08-17 Cleanups for less decoupler capacitors
2017-08-17 Cleanups for current setup
2017-08-18 Local 3D shape copy for solid PCB 3D view
2017-08-18 Removed extra outlines
2017-08-18 Corrected model for proper 3D display
2017-08-18 Adjusted to local 3D shape copies for consistent 3D view
2017-08-18 Slight adjustments
2017-08-18 Local copy
2017-08-18 Slightly corrected
2017-08-19 Moved folder to the new name
2017-08-19 Corrected 3D shape to a local copy
2017-08-19 Corrected 3D shape to a local copy with proper size
2017-08-19 Work in progress
2017-08-19 Renamed folder
2017-08-19 Moved to Schematics folder
2017-08-20 Background fill for LC125
2017-08-20 Local copy 3 pin SMT pads
2017-08-20 Joystick interface added
2017-08-20 Local copy, BAC54 used as reference
2017-08-20 Updated 3D shape with local copy
2017-08-20 Minor updates
2017-08-20 Work in progress, updated 3D shapes
2017-08-20 3D shapes local copy
2017-08-20 VTERM decouple capacitors added
2017-08-20 Changes to decoupler capacitor quantity and nets
2017-08-20 Digital Video Clock singal moved closer
2017-08-21 Output filter for Audio DAC added
2017-08-21 Hard link library for any project settings
2017-08-21 Design Rules set according to my Fab House, switching to 4 layer board
2017-08-21 Hard link for N64 lib
2017-08-21 Initial board layout
2017-08-21 Initial project settings
2017-08-21 Peripherial copy, todo: remove extra circuits
2017-08-21 New initial schematics for DAC and Amplifier section
2017-08-21 Audio DAC moved to a separate project
2017-08-21 Auto libs changes
2017-08-21 Libname adjusted to a local hardlink copy
2017-08-21 New Design Rules for my Fab, inner power layers added
2017-08-22 Removed Audio DAC
2017-08-22 Corrected Audio Out for Digital interfacing
2017-08-22 Corrected marshallh name
2017-08-22 Temperature monitoring
2017-08-24 Power consumption measurements notes added
2017-08-24 Proper folder name
2017-08-24 Renamed to PCB-Designs
2017-08-24 Another power supply board
2017-08-24 U3 added for soft-start feature
2017-08-24 PLL capacitors size corrected
2017-08-25 MX8330 footprint, named after datasheet suggestion
2017-08-25 Remade to SOP-8
2017-08-25 VTERM/VREF current measurements commented
2017-08-25 This contains more or less modern IC
2017-08-25 It looks like correct U3 chip, NUS-CPU-04 reads 2870 on the IC body
2017-08-25 Renamed
2017-08-25 Unused so far
2017-08-25 VDC-NUS
2017-08-25 Riddance in favour of pif-nus-so-28w
2017-08-25 Adjusted and confirmed to fit actual ICs
2017-08-25 Adjusted according datasheet, TODO: confirm with real IC
2017-08-25 Slight adjustments, WIP
2017-08-26 Unused
2017-08-26 Moved to MX8300-U5
2017-08-26 Corrected and verified against real CPU
2017-08-26 Slight changes
2017-08-26 Reference field fixed
2017-08-26 Renamed to pqfp-64
2017-08-26 Preliminary 3D shape
2017-08-26 CNT-NUS 3D shape source, WIP
2017-08-27 Corrected to fit freshly created 3D shape
2017-08-27 Source file for PQFP-64 package, completed
2017-08-27 Riddance of old stuff
2017-08-27 Slight re-arrangements
2017-08-27 Re-arranged, rewired, changed sizes and renamed decoupling capacitors
2017-08-27 Newer version according to modified schematics, need slight updates on Silk Screen
2017-08-28 Solder switch for RDRAM board
2017-08-28 Notes added
2017-08-28 4 layers WIP
2017-08-28 Finished 4 layer board
2017-08-28 Finished 4 layer board with Gerber output settings
2017-08-28 Updated design rules
2017-08-28 Updated design rules for better fab pricing, corrected to comply DRC
2017-08-29 R36 and C144 moved here for ENABLE signal
2017-08-29 R36 and C144 moved from here
2017-08-29 Changed to symlink instead
2017-08-29 Corrected symlink
2017-08-29 Changed ENABLE to ENABLE_CLK due to correction in ENABLE generation
2017-08-29 Current project settings
2017-08-29 Footprints re-assigned
2017-08-29 Another rebuild, WIP
2017-08-29 FCP cart WIP
2017-08-29 Work in progress, pinout for gamepak flat cable
2017-08-29 50 pins FCP connector in progress
2017-08-30 20 pin FCP for gamepak power lines
2017-08-30 Adjusted gamepak FCP connections, joystick port
2017-08-30 Proper Molex FCP 50 pin layout for gamepak
2017-08-30 Better layout, work in progress
2017-08-30 Wire wire line
2017-08-30 Decoupling C134 added
2017-08-30 Sub-sheets title text increased
2017-08-30 Laying around, cleanier look
2017-08-31 Outer layer GND fillzone added, TODO re-plot gerber files
2017-08-31 This in use instead of TUMD2
2017-08-31 Not in use anymore
2017-08-31 D2 footprint changed to 0805
2017-09-03 Done, ERC passed, just need additional confirmation
2017-09-03 Routing in progress, almost completed
2017-09-03 CART EDGE CIC have been made bi-directional to satisfy ERC in rcp-cart schematics
2017-09-03 Completed, to do checks
2017-09-04 Via for stitching power zones
2017-09-04 No waste logo local copy
2017-09-04 PCB look
2017-09-04 Updated PCB look
2017-09-04 Fabricatin files
2017-09-04 Better description
2017-09-04 Pictures added
2017-09-04 RDRAM edge, PLL, PIF, LC125 and most decoupling capacitors aligned
2017-09-04 not sure, actually...
2017-09-05 CART FLAT CABLE mirrored
2017-09-06 More alignments
2017-09-06 Not in use any more
2017-09-06 DC input
2017-09-06 PQ7VZ5 LDO added
2017-09-06 Wrong footprint
2017-09-06 New power input connector
2017-09-06 3D shape for DC input
2017-09-06 C37 VTERM local decoupling added
2017-09-06 R36 and C144 are moved to peripherials sheet
2017-09-07 More alignments and tracks
2017-09-07 More RCP tracks alignments
2017-09-07 CR17 added
2017-09-07 CPU to RCP routing completed
2017-09-08 Verified against physical slot
2017-09-08 Fixing in progress for new CART EDGE footprint
2017-09-09 Most of tracks are tuned down to 0.2mm, updated design rules
2017-09-09 Started to route CPU power wiring
2017-09-09 RCP power wiring is done, todo clock enable
2017-09-10 Basic layout finished, to do checks and tune ups
2017-09-10 Rev.3
2017-09-10 Fabrication files
2017-09-10 Updated with Core Board picture, fixed other boards pictures
2017-09-10 Moved to now more appropriate place
2017-09-12 New fabrication file
2017-09-12 VTERM moved to inner 3V3 layer, added few GND stitch vias, board silkscreen signature
2017-09-13 STEP variant
2017-09-14 STEP source from Molex website
2017-09-16 3D shapes for FreeCAD-PCB mod
2017-09-16 Boards assembly file
